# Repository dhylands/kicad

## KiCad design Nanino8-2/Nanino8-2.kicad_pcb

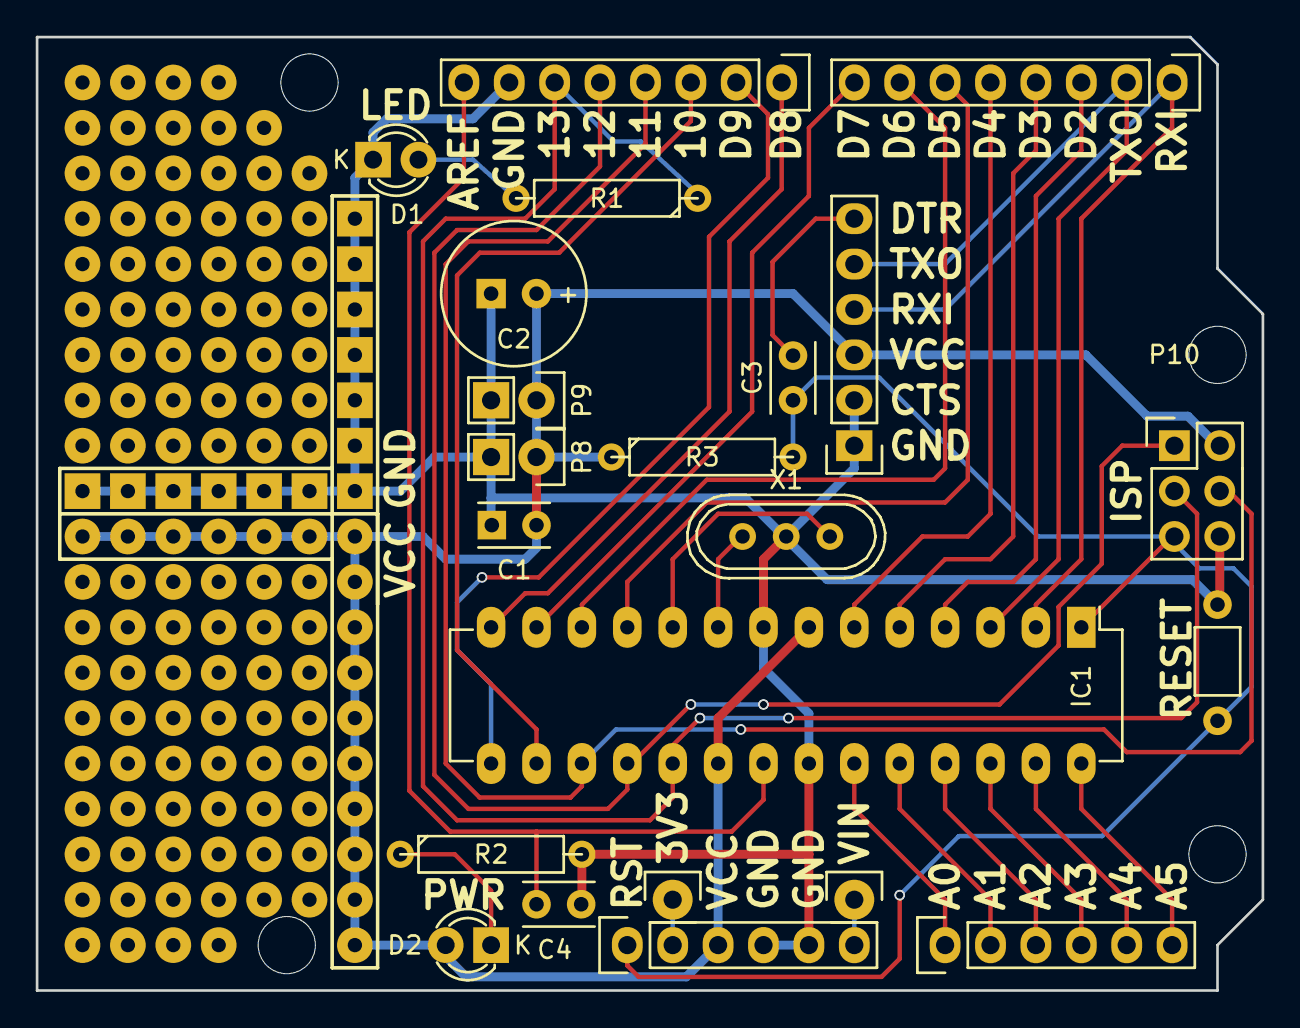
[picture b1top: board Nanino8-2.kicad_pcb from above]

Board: 2 copper layers, 68.6 x 53.3 mm, 23 parts (0 on the bottom side), 31 nets.

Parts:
C1, C3, C4: 0.1uF; C_Rect_L4_W2.5_P2.5_Mill
C2: 10uF; C1V8
D1: LED; LED-3MM
D2: POWER; LED-3MM
IC1: ATMEGA328-P; DIP-28_W7.62mm_LongPads
P1: POWER; Pin_Header_Straight_1x06
P2: ANALOG; Pin_Header_Straight_1x06
P3: SERIAL; Pin_Header_Straight_1x06
P4: DIGITAL 0-7; Pin_Header_Straight_1x08
P5: DIGITAL 8-13; Pin_Header_Straight_1x08
P6: 3V3; Pin_Header_Straight_1x01
P7: VIN; Pin_Header_Straight_1x01
P8, P9: CONN_01X02; Pin_Header_Straight_1x02
P10: ISP; Pin_Header_Straight_2x03
R1, R2: 1k; R4
R3: 10k; R4
SW1: SW_PUSH; SW_PUSH-2pin-6.5mm
X1: 16 MHz; Resonator
xREF**: SolderWirePad_single_0-8mmDrill

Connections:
/3V3: P1.2, P6.1
/A0: IC1.23, P2.1
/A1: IC1.24, P2.2
/A2: IC1.25, P2.3
/A3: IC1.26, P2.4
/A4: IC1.27, P2.5
/A5: IC1.28, P2.6
/D2: IC1.4, P4.3
/D3: IC1.5, P4.4
/D4: IC1.6, P4.5
/D5: IC1.11, P4.6
/D6: IC1.12, P4.7
/D7: IC1.13, P4.8
/D8: IC1.14, P5.1
/D9: IC1.15, P5.2
/D10: IC1.16, P5.3
/RXD: IC1.2, P3.4, P4.1
/TXD: IC1.3, P3.5, P4.2
/VIN: P1.6, P7.1
AREF: C4.1, IC1.21, P5.8
DTR: C3.2, P3.6
GND: C1.2, C2.2, C4.2, D1.1, IC1.8, IC1.22, P1.4, P1.5, P3.1, P3.2, P5.7, P8.2, P9.2, P10.6, R2.2, SW1.1, X1.2, xREF**.1
LED: IC1.19, P5.6, P10.3, R1.1
MISO: IC1.18, P5.5, P10.1
MOSI: IC1.17, P5.4, P10.4
unnamed: D1.2, R1.2
unnamed: D2.1, R2.1
RESET: C3.1, IC1.1, P1.1, P10.5, R3.2, SW1.2
VCC: C1.1, C2.1, D2.2, IC1.7, IC1.20, P1.3, P3.3, P8.1, P9.1, P10.2, R3.1
X1: IC1.9, X1.1
X2: IC1.10, X1.3

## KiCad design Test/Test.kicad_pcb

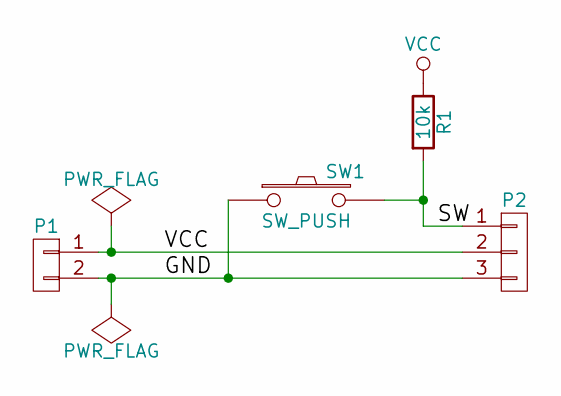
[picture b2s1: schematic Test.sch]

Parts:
P1: CONN_01X02; Pin_Header_Straight_1x02
P2: CONN_01X03; Pin_Header_Straight_1x03
R1: 10k; R4
SW1: SW_PUSH

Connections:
/GND: P1.2, P2.3, SW1.1
/SW: P2.1, R1.2, SW1.2
VCC: P1.1, P2.2, R1.1

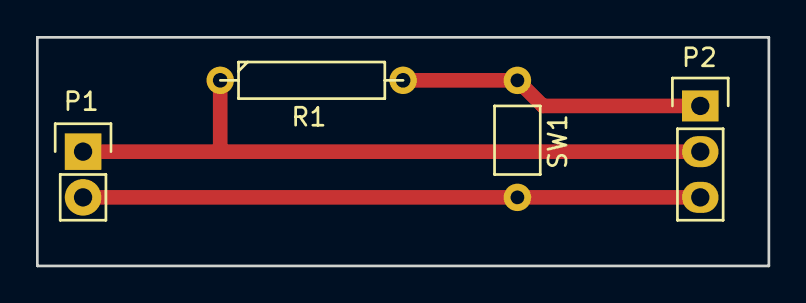
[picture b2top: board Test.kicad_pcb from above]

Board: 2 copper layers, 40.6 x 12.7 mm, 4 parts (0 on the bottom side), 3 nets.

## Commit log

2016-08-08 Initial checkin
2016-08-08 Added Nanino8 BOM cost
2016-08-09 Generated gerbers
2016-08-25 Updated for Course Session 1
2016-08-28 Designed a variation of Nanino8
    This is my backup plan for the PCB course
    just in case the PCB engraving doesn't work.
2016-08-29 Added rename-gerbers.py script for DirtyPCBs.
2016-09-16 Added python helper scripts
2016-09-16 Relocted origin
2016-12-08 Addec part 2 & 3 course notes
